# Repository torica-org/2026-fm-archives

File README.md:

# 2026-fm-archives
26代機REWRITE搭載電装のフライトモデル(FM)

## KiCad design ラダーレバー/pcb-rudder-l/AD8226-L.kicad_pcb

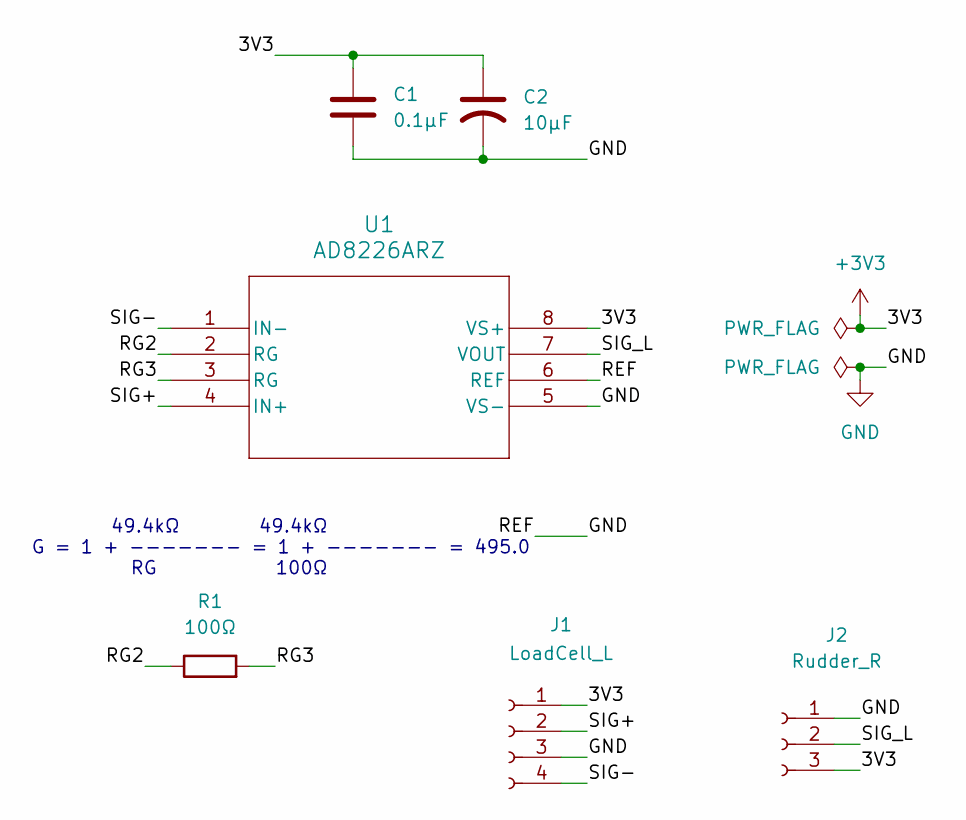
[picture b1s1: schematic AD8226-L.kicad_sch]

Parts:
C1: 0.1μF; C_0603_1608Metric_Pad1.08x0.95mm_HandSolder
C2: 10μF; C_0603_1608Metric_Pad1.08x0.95mm_HandSolder
J1: LoadCell_L; PA_Connector_Post_4pin_Side
J2: Rudder_R; PA_Connector_Post_3Pin_Side
R1: 100Ω; R_0805_2012Metric_Pad1.20x1.40mm_HandSolder
U1: AD8226ARZ; R_8_ADI

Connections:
+3V3: C1.1, C2.1, J1.1, J2.3, U1.8 (VS+)
/RG2: R1.1, U1.2 (RG)
/RG3: R1.2, U1.3 (RG)
/SIG+: J1.2, U1.4 (IN+)
/SIG-: J1.4, U1.1 (IN-)
/SIG_L: J2.2, U1.7 (VOUT)
GND: C1.2, C2.2, J1.3, J2.1, U1.5 (VS-), U1.6 (REF)

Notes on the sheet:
49.4kΩ 49.4kΩ G = 1 + ------- = 1 + ------- = 495.0 RG 100Ω

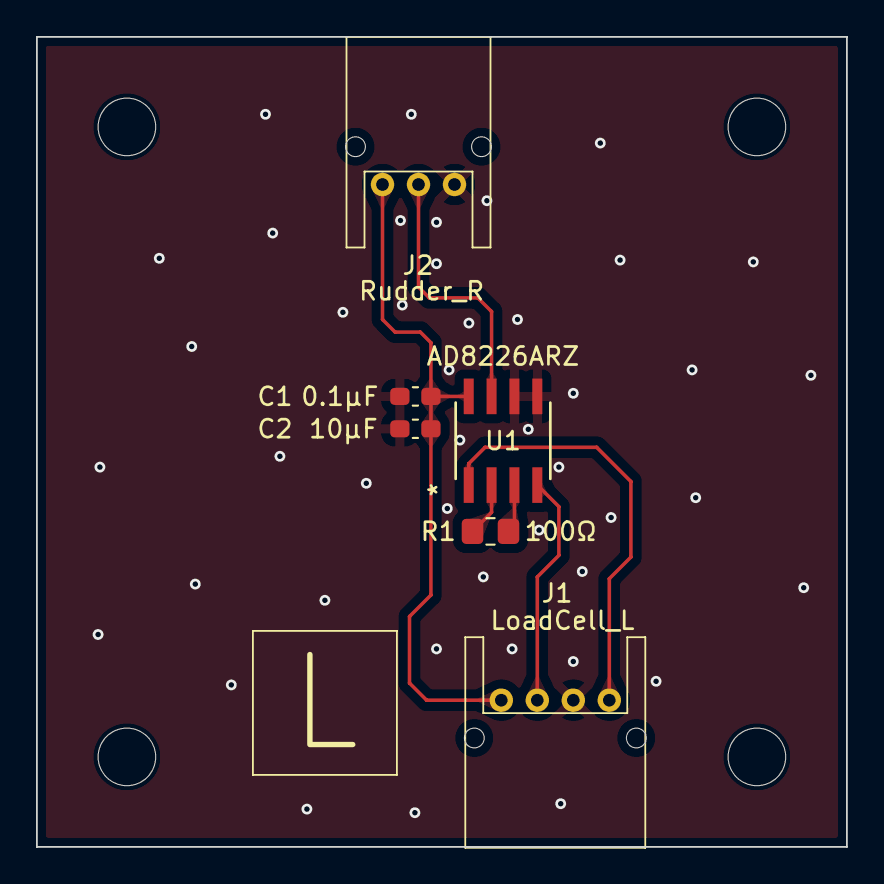
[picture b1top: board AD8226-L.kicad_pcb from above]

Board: 2 copper layers, 45.0 x 45.0 mm, 6 parts (0 on the bottom side), 7 nets.

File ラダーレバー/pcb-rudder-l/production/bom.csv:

Designator,Footprint,Quantity,Value,LCSC Part #
C1,0603,1,0.1μF,
C2,0603,1,10μF,
J1,PA_Connector_Post_4pin_Side,1,LoadCell_L,
J2,PA_Connector_Post_3Pin_Side,1,Rudder_R,
R1,0805,1,100Ω,
U1,R_8_ADI,1,AD8226ARZ,
